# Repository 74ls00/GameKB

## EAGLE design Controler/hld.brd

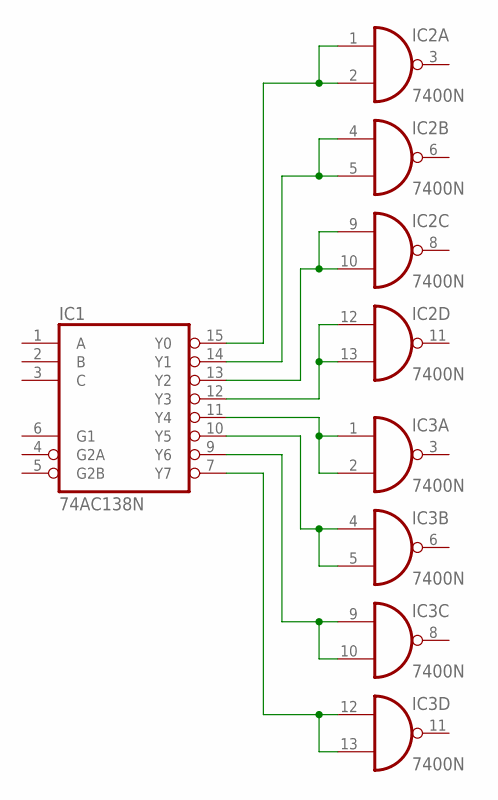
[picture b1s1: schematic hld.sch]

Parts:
IC1: 74AC138N; DIL16
IC2, IC3: 7400N; DIL14

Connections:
GND: IC1.8 (GND), IC2.7 (GND), IC3.7 (GND)
unnamed: IC1.15 (Y0), IC2.1 (I0), IC2.2 (I1)
unnamed: IC1.14 (Y1), IC2.4 (I0), IC2.5 (I1)
unnamed: IC1.13 (Y2), IC2.9 (I0), IC2.10 (I1)
unnamed: IC1.12 (Y3), IC2.12 (I0), IC2.13 (I1)
unnamed: IC1.11 (Y4), IC3.1 (I0), IC3.2 (I1)
unnamed: IC1.10 (Y5), IC3.4 (I0), IC3.5 (I1)
unnamed: IC1.9 (Y6), IC3.9 (I0), IC3.10 (I1)
unnamed: IC1.7 (Y7), IC3.12 (I0), IC3.13 (I1)
VCC: IC1.16 (VCC), IC2.14 (VCC), IC3.14 (VCC)

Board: 2 copper layers, 3 parts (0 on the bottom side), 10 nets, no tracks yet.

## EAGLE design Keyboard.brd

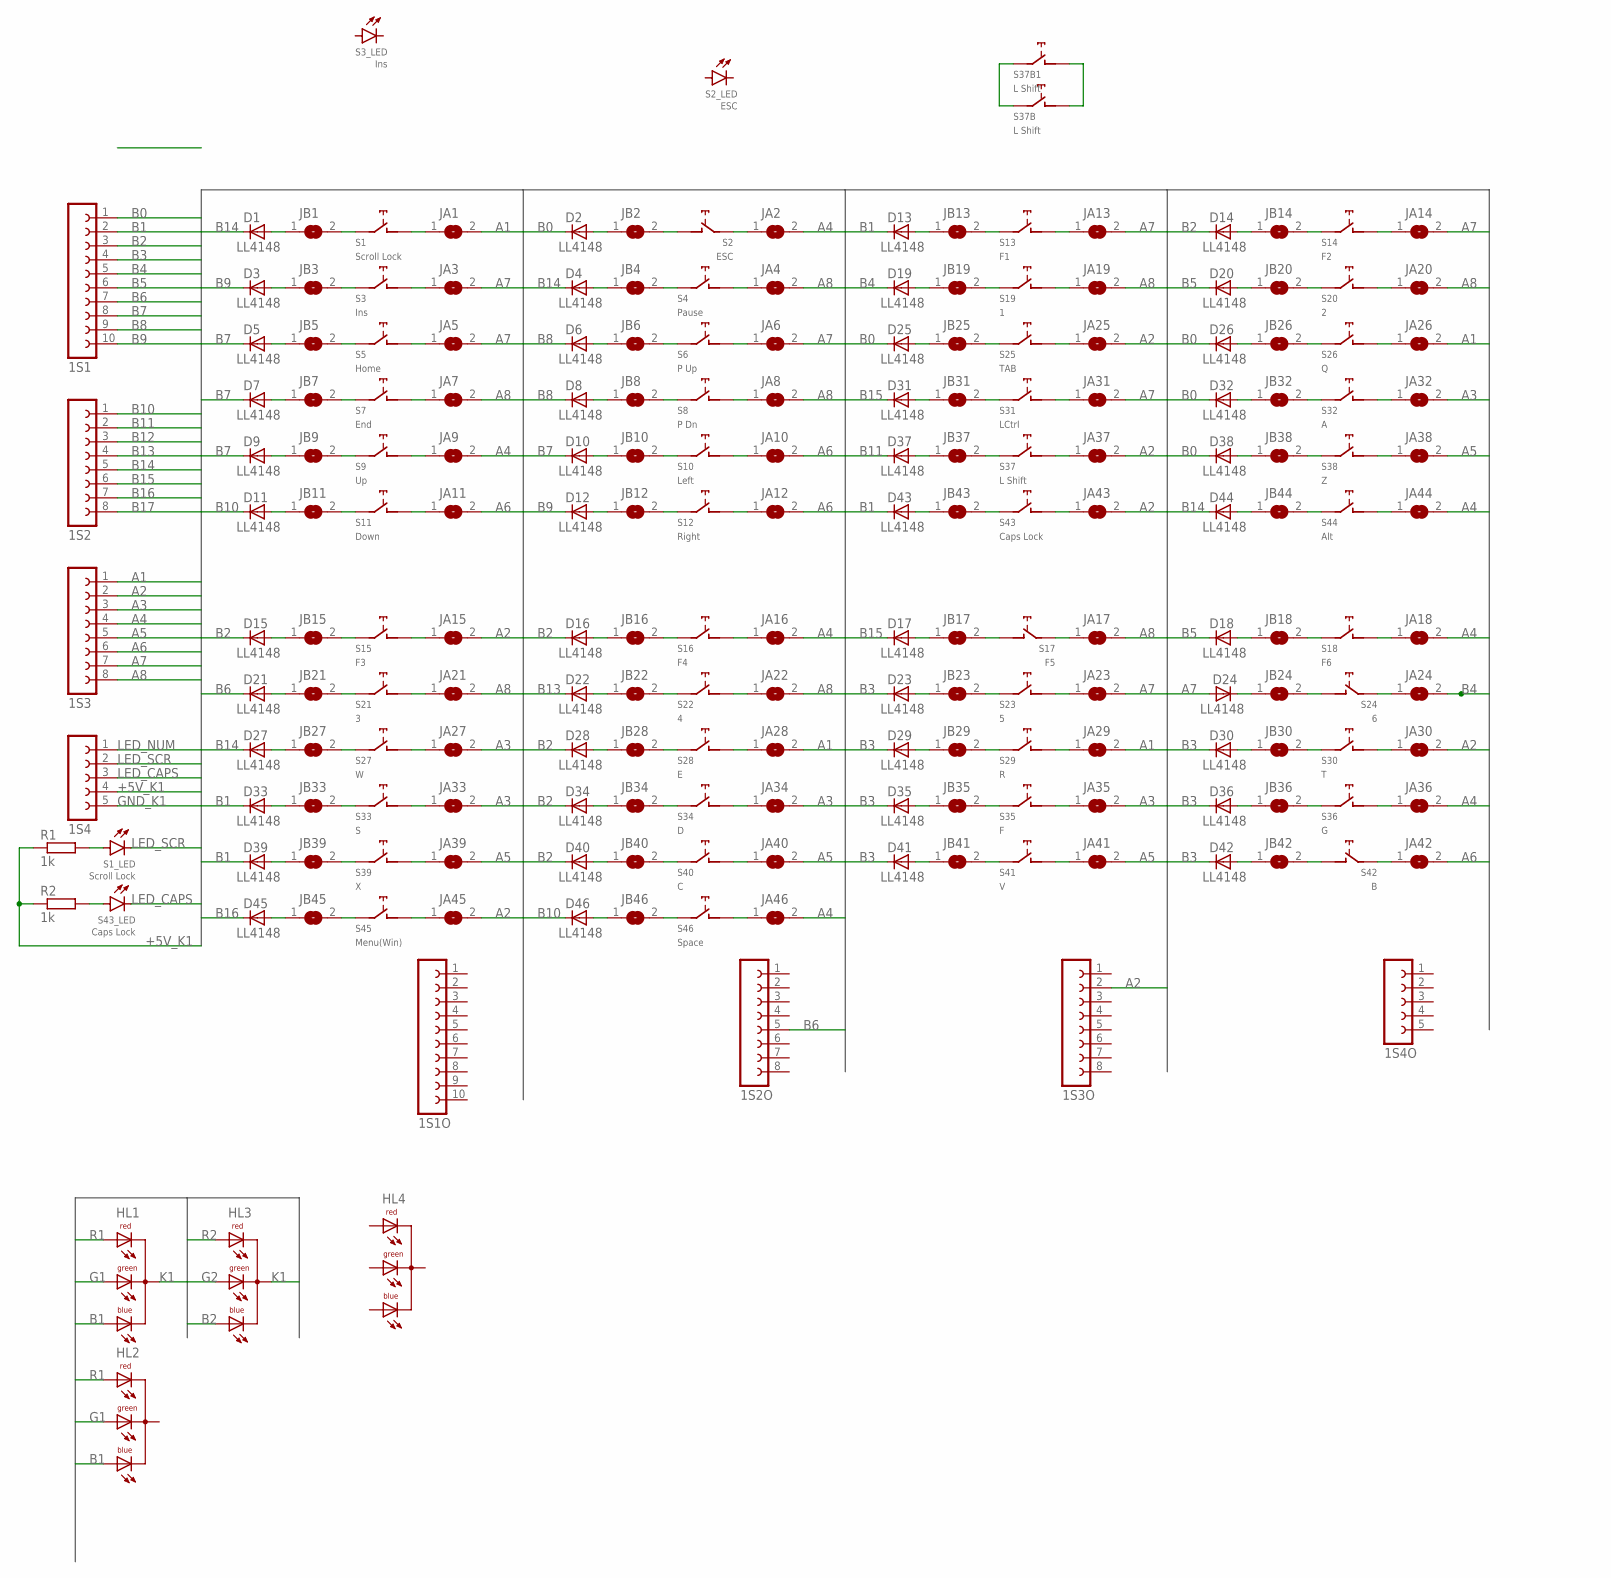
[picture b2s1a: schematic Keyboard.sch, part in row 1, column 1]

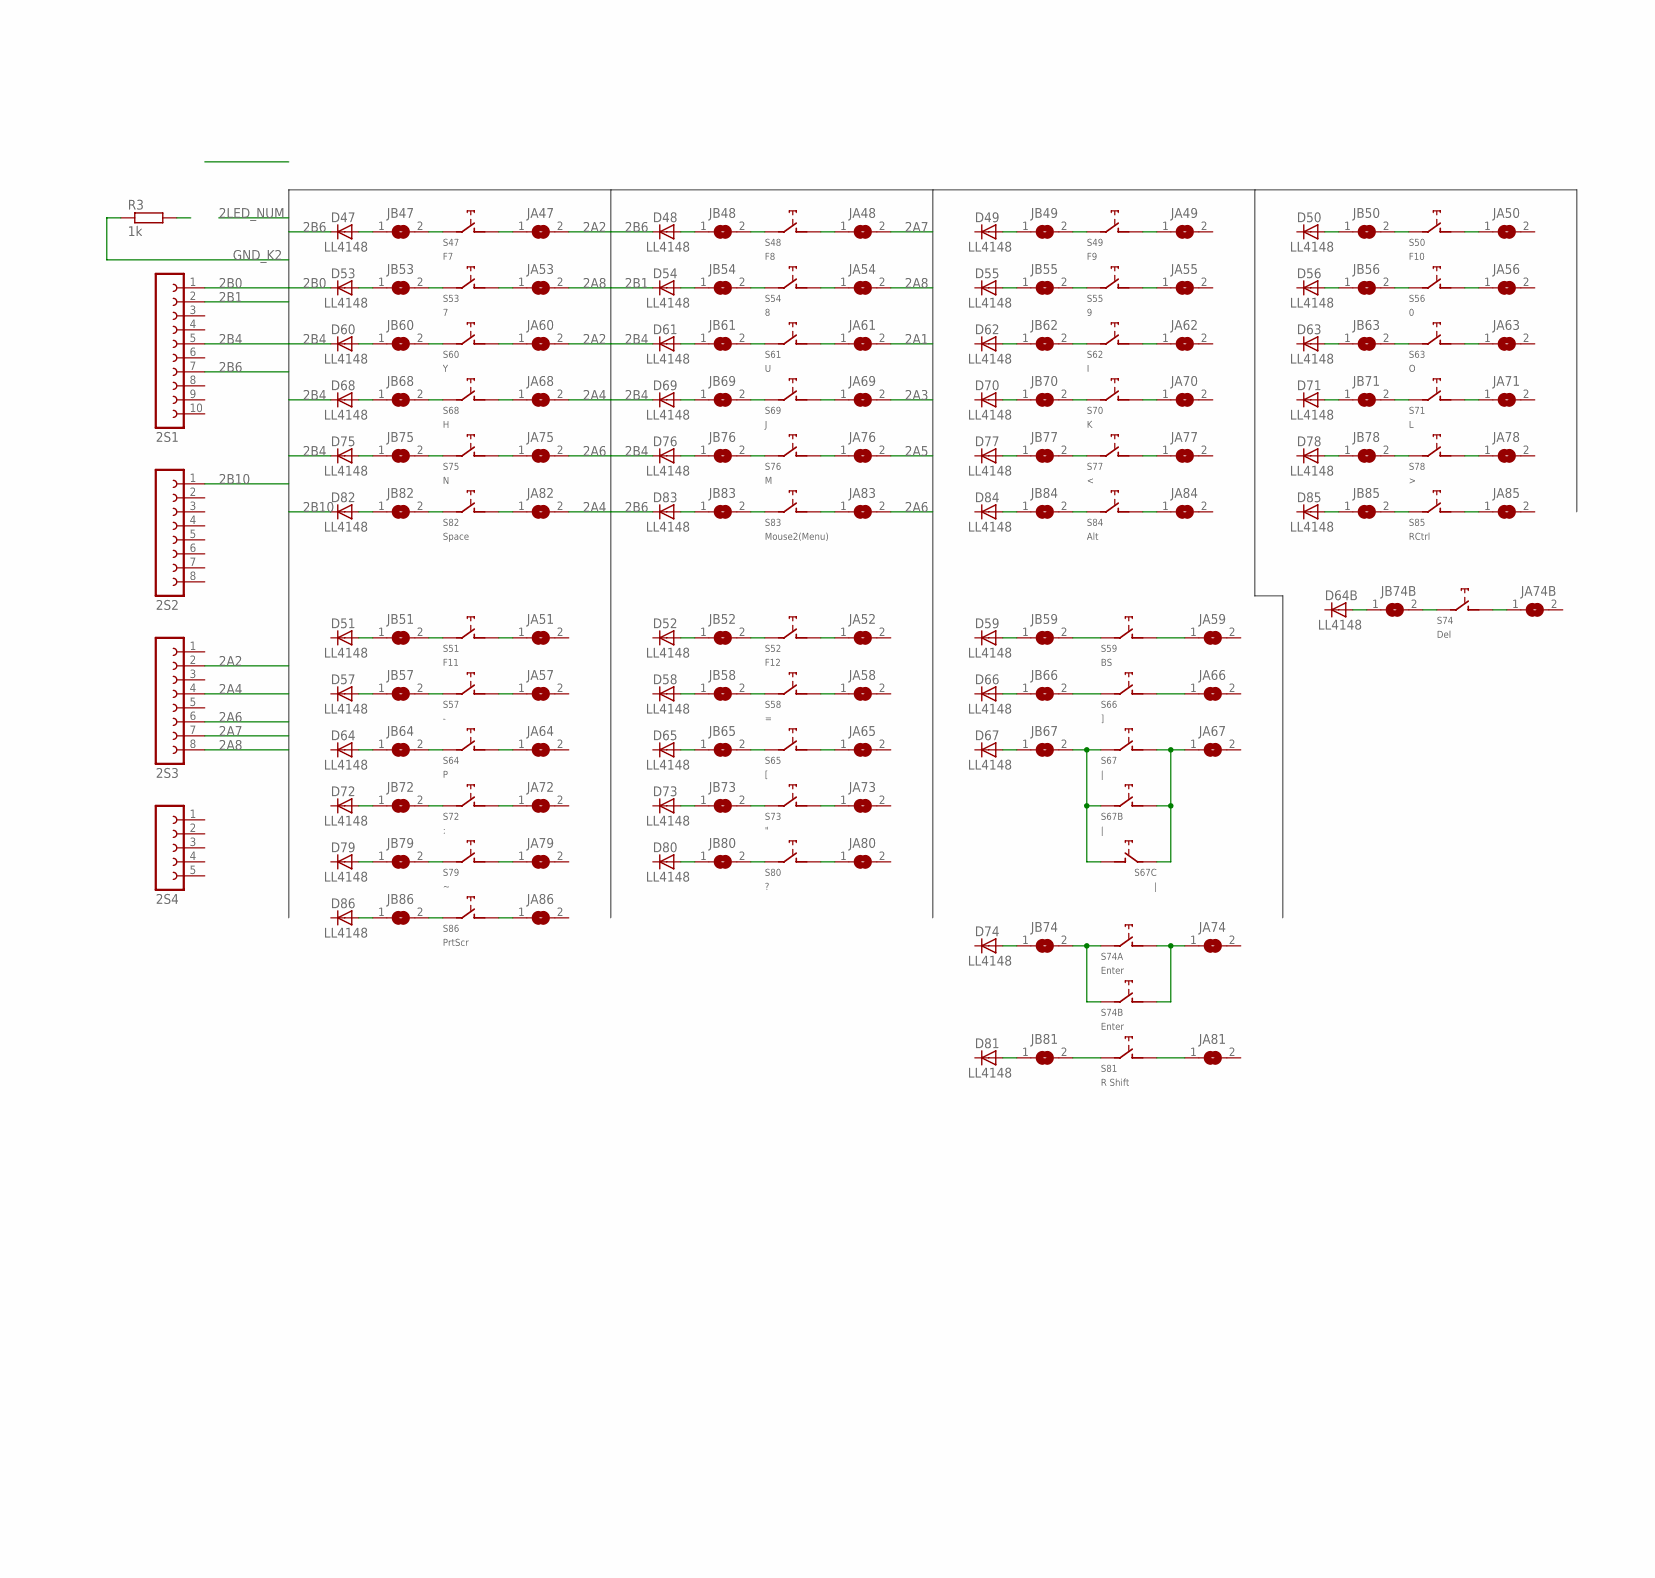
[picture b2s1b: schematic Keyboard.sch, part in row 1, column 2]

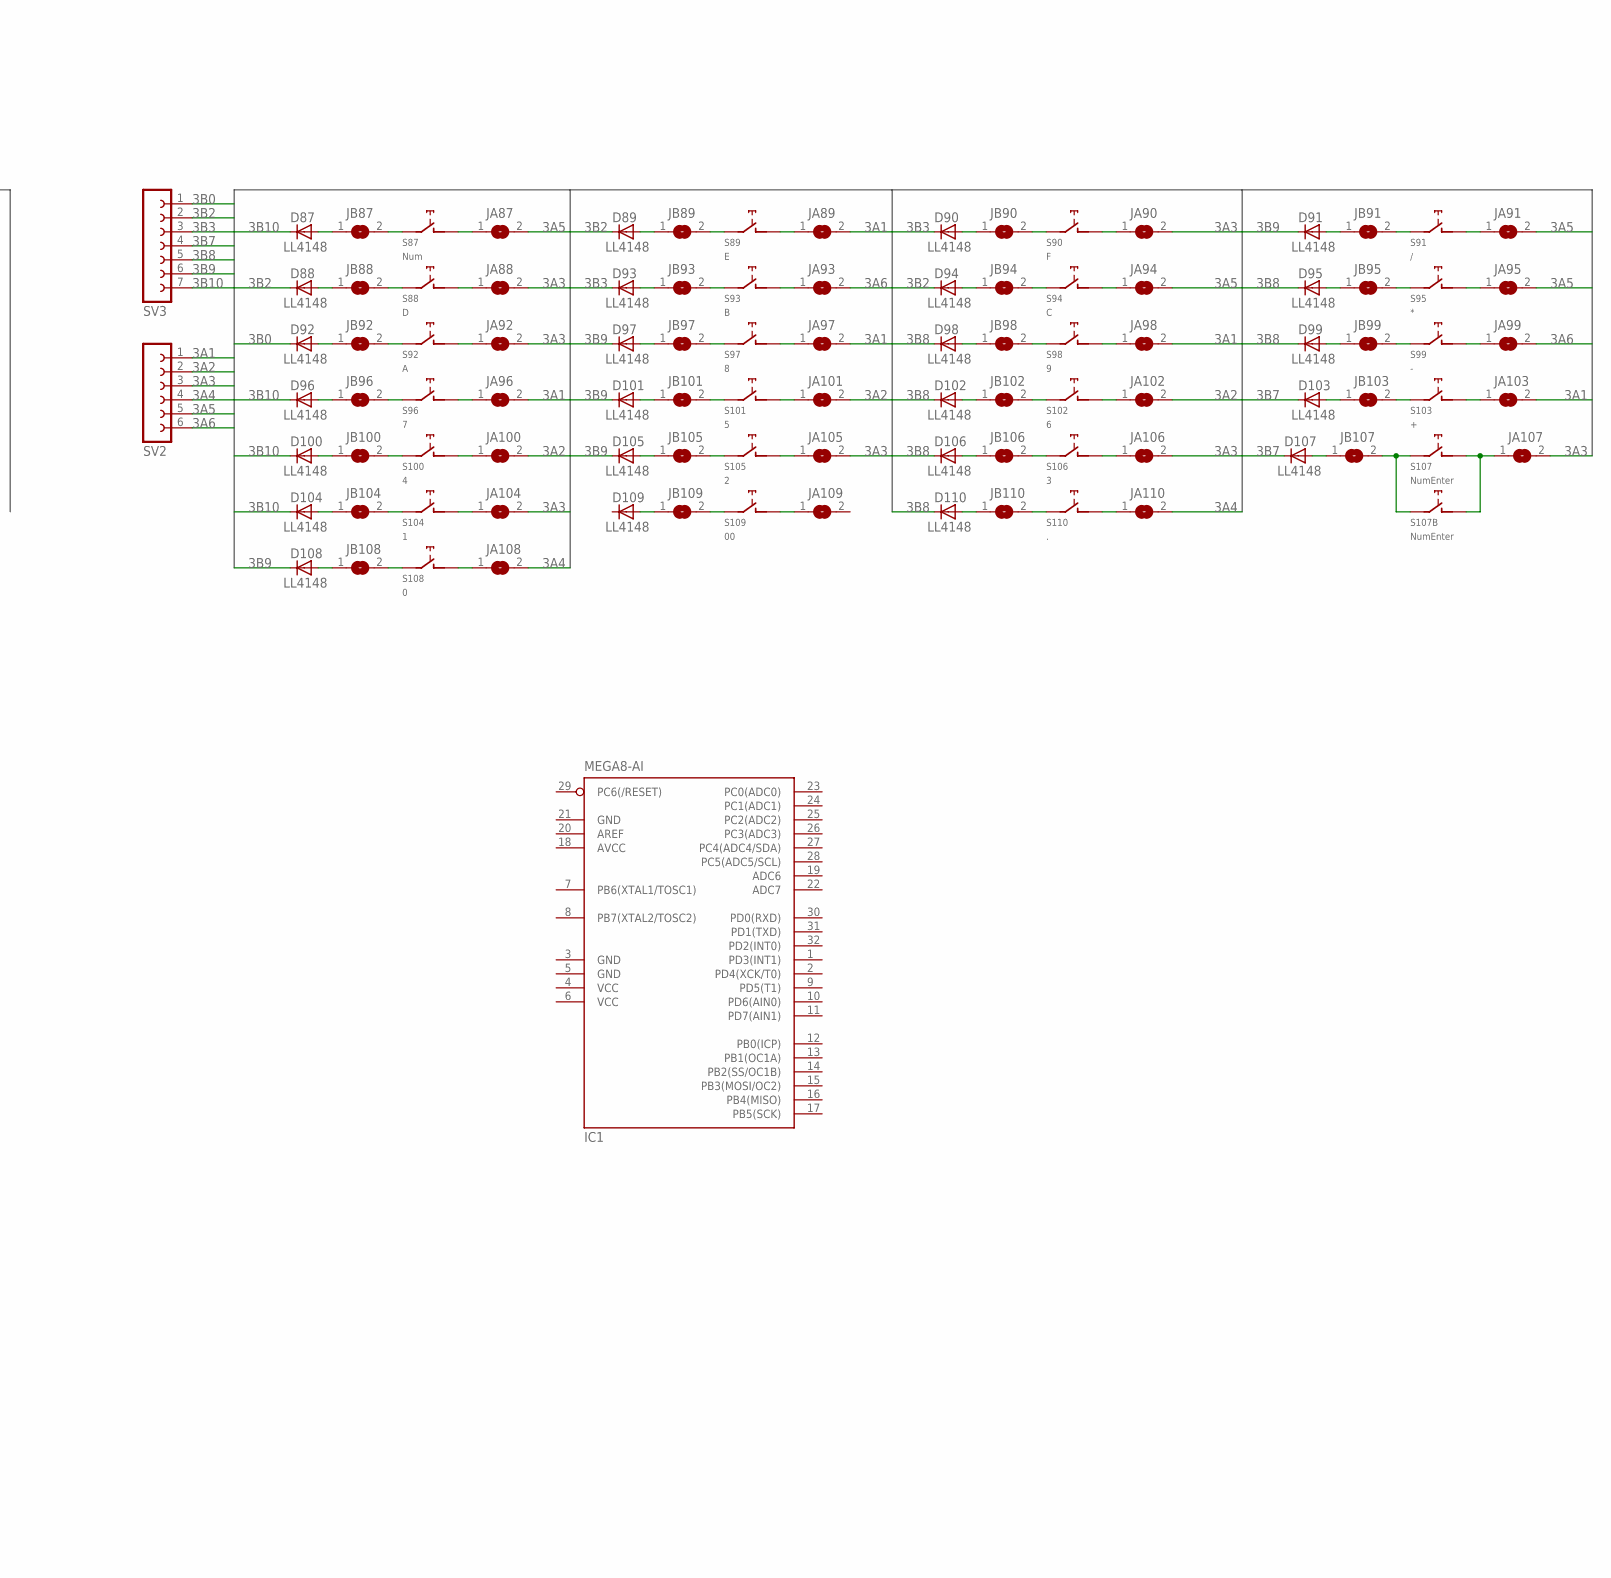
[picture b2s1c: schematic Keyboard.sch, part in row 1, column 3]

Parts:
1S1, 1S1O, 2S1: FE10-1; FE10
1S2, 1S2O, 1S3, 1S3O, 2S2, 2S3: FE08-1; FE08
1S4, 1S4O, 2S4: FE05-1
D1, D2, D3, D4, D5, D6, D7, D8, D9, D10, D11, D12, D13, D14, D15, D16, D17, D18, D19, D20, D21, D22, D23, D24, D25, D26, D27, D28, D29, D30, D31, D32, D33, D34, D35, D36, D37, D38, D39, D40, D41, D42, D43, D44, D45, D46, D47, D48, D49, D50, D51, D52, D53, D54, D55, D56, D57, D58, D59, D60, D61, D62, D63, D64, D64B, D65, D66, D67, D68, D69, D70, D71, D72, D73, D74, D75, D76, D77, D78, D79, D80, D81, D82, D83, D84, D85, D86, D87, D88, D89, D90, D91, D92, D93, D94, D95, D96, D97, D98, D99, D100, D101, D102, D103, D104, D105, D106, D107, D108, D109, D110: LL4148; SOD80C
HL1, HL2, HL3, HL4: RGB2X5
IC1: MEGA8-AI; TQFP32-08
JA1, JA2, JA3, JA4, JA5, JA6, JA7, JA8, JA9, JA10, JA11, JA12: SJ; SJ@1
JA13, JA14, JA15, JA16, JA17, JA18, JA19, JA20, JA21, JA22, JA23, JA24, JA25, JA26, JA27, JA28, JA29, JA30, JA31, JA32, JA33, JA34, JA35, JA36, JA37, JA38, JA39, JA40, JA41, JA42, JA43, JA44, JA45, JA46, JA47, JA48, JA49, JA50, JA51, JA52, JA53, JA54, JA55, JA56, JA57, JA58, JA59, JA60, JA61, JA62, JA63, JA64, JA65, JA66, JA67, JA68, JA69, JA70, JA71, JA72, JA73, JA74, JA74B, JA75, JA76, JA77, JA78, JA79, JA80, JA81, JA82, JA83, JA84, JA85, JA86, JA87, JA88, JA89, JA90, JA91, JA92, JA93, JA94, JA95, JA96, JA97, JA98, JA99, JA100, JA101, JA102, JA103, JA104, JA105, JA106, JA107, JA108, JA109, JA110: SJ
JB1, JB3, JB18, JB19, JB20, JB21, JB22, JB23, JB24, JB25, JB26, JB27, JB28, JB29, JB30, JB31, JB32, JB33, JB34, JB35, JB36, JB37, JB38, JB39, JB40, JB41, JB42, JB43, JB44, JB45, JB46, JB47, JB48, JB49, JB50, JB51, JB52, JB53, JB54, JB55, JB56, JB57, JB58, JB59, JB60, JB61, JB62, JB63, JB64, JB65, JB66, JB67, JB68, JB69, JB70, JB71, JB72, JB73, JB74, JB74B, JB75, JB76, JB77, JB78, JB79, JB80, JB81, JB82, JB83, JB84, JB85, JB86, JB87, JB88, JB89, JB90, JB91, JB92, JB93, JB94, JB95, JB96, JB97, JB98, JB99, JB100, JB101, JB102, JB103, JB104, JB105, JB106, JB107, JB108, JB109, JB110: SJ
JB2, JB4, JB5, JB6, JB7, JB8, JB9, JB10, JB11, JB12, JB13, JB14, JB15, JB16, JB17: SJ; SJ@1
R1, R2: 1k; R1206W
R3: 1k; R0805
S1: Scroll Lock; CHERRY-MX-LED
S2: ESC; CHERRY-MX-LED
S3: Ins; CHERRY-MX-LED
S4: Pause; CHERRY-MX@1
S5: Home; CHERRY-MX
S6: P Up; CHERRY-MX
S7: End; CHERRY-MX
S8: P Dn; CHERRY-MX
S9: Up; CHERRY-MX
S10: Left; CHERRY-MX
S11: Down; CHERRY-MX
S12: Right; CHERRY-MX
S13: F1; CHERRY-MX
S14: F2; CHERRY-MX
S15: F3; CHERRY-MX
S16: F4; CHERRY-MX
S17: F5; CHERRY-MX
S18: F6; CHERRY-MX
S19: 1; CHERRY-MX
S20: 2; CHERRY-MX
S21: 3; CHERRY-MX
S22: 4; CHERRY-MX
S23: 5; CHERRY-MX
S24: 6; CHERRY-MX
S25: TAB; CHERRY-MX
S26: Q; CHERRY-MX
S27: W; CHERRY-MX@1
S28: E; CHERRY-MX
S29: R; CHERRY-MX
S30: T; CHERRY-MX
S31: LCtrl; CHERRY-MX
S32: A; CHERRY-MX
S33: S; CHERRY-MX
S34: D; CHERRY-MX
S35: F; CHERRY-MX
S36: G; CHERRY-MX
S37, S37B, S37B1: L Shift; CHERRY-MX
S38: Z; CHERRY-MX
S39: X; CHERRY-MX
S40: C; CHERRY-MX
S41: V; CHERRY-MX
S42: B; CHERRY-MX
S43: Caps Lock; CHERRY-MX-LED
S44, S84: Alt; CHERRY-MX
S45: Menu(Win); CHERRY-MX
S46, S82: Space; CHERRY-MX
S47: F7; CHERRY-MX
S48: F8; CHERRY-MX
S49: F9; CHERRY-MX
S50: F10; CHERRY-MX
S51: F11; CHERRY-MX
S52: F12; CHERRY-MX
S53: 7; CHERRY-MX
S54: 8; CHERRY-MX
S55: 9; CHERRY-MX
S56: 0; CHERRY-MX
S57: -; CHERRY-MX
S58: =; CHERRY-MX
S59: BS; CHERRY-MX
S60: Y; CHERRY-MX
S61: U; CHERRY-MX
S62: I; CHERRY-MX
S63: O; CHERRY-MX
S64: P; CHERRY-MX
S65: [; CHERRY-MX
S66: ]; CHERRY-MX
S67, S67B, S67C: |; CHERRY-MX
S68: H; CHERRY-MX
S69: J; CHERRY-MX
S70: K; CHERRY-MX
S71: L; CHERRY-MX
S72: :; CHERRY-MX
S73: "; CHERRY-MX
S74: Del; CHERRY-MX
S74A, S74B: Enter; CHERRY-MX
S75: N; CHERRY-MX
S76: M; CHERRY-MX
S77: <; CHERRY-MX
S78: >; CHERRY-MX
S79: CHERRY-MX
S80: ?; CHERRY-MX
S81: R Shift; CHERRY-MX
S83: Mouse2(Menu); CHERRY-MX
S85: RCtrl; CHERRY-MX
S86: PrtScr; CHERRY-MX
S87: Num; CHERRY-MX-4P
S88: D; CHERRY-MX-4P
S89: E; CHERRY-MX-4P
S90: F; CHERRY-MX-4P
S91: /; CHERRY-MX-4P
S92: A; CHERRY-MX-4P
S93: B; CHERRY-MX-4P
S94: C; CHERRY-MX-4P
S95: *; CHERRY-MX-4P
S96: 7; CHERRY-MX-4P
S97: 8; CHERRY-MX-4P
S98: 9; CHERRY-MX-4P
S99: -; CHERRY-MX-4P
S100: 4; CHERRY-MX-4P
S101: 5; CHERRY-MX-4P
S102: 6; CHERRY-MX-4P
S103: +; CHERRY-MX-4P
S104: 1; CHERRY-MX-4P
S105: 2; CHERRY-MX-4P
S106: 3; CHERRY-MX-4P
S107: NumEnter; CHERRY-MX-4P
S107B: NumEnter; CHERRY-MX
S108: 0; CHERRY-MX-4P
S109: 00; CHERRY-MX-4P
S110: .; CHERRY-MX-4P
SV2: FE06-1; FE06
SV3: FE07-1; FE07

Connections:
2A1: JA61.2
2A2: 2S3.2, JA47.2, JA60.2
2A3: JA69.2
2A4: 2S3.4, JA68.2, JA82.2
2A5: JA76.2
2A6: 2S3.6, JA75.2, JA83.2
2A7: 2S3.7, JA48.2
2A8: 2S3.8, JA53.2, JA54.2
2B0: 2S1.1, D53.C
2B1: 2S1.2, D54.C
2B4: 2S1.5, D60.C, D61.C, D68.C, D69.C, D75.C, D76.C
2B6: 2S1.7, D47.C, D48.C, D83.C
2B10: 2S2.1, D82.C
3A1: JA89.2, JA96.2, JA97.2, JA98.2, JA103.2, SV2.1
3A2: JA100.2, JA101.2, JA102.2, SV2.2
3A3: JA88.2, JA90.2, JA92.2, JA104.2, JA105.2, JA106.2, JA107.2, SV2.3
3A4: JA108.2, JA110.2, SV2.4
3A5: JA87.2, JA91.2, JA94.2, JA95.2, SV2.5
3A6: JA93.2, JA99.2, SV2.6
3B0: D92.C, SV3.1
3B2: D88.C, D89.C, D94.C, SV3.2
3B3: D90.C, D93.C, SV3.3
3B7: D103.C, D107.C, SV3.4
3B8: D95.C, D98.C, D99.C, D102.C, D106.C, D110.C, SV3.5
3B9: D91.C, D97.C, D101.C, D105.C, D108.C, SV3.6
3B10: D87.C, D96.C, D100.C, D104.C, SV3.7
+5V_K1: 1S4.4, R1.1, R2.1
A1: 1S3.1, JA1.2, JA26.2, JA28.2, JA29.2
A2: 1S3.2, 1S3O.2, JA15.2, JA25.2, JA30.2, JA37.2, JA43.2, JA45.2
A3: 1S3.3, JA27.2, JA32.2, JA33.2, JA34.2, JA35.2
A4: 1S3.4, JA2.2, JA9.2, JA16.2, JA18.2, JA36.2, JA44.2, JA46.2
A5: 1S3.5, JA38.2, JA39.2, JA40.2, JA41.2
A6: 1S3.6, JA10.2, JA11.2, JA12.2, JA42.2
A7: 1S3.7, D24.A, JA3.2, JA5.2, JA6.2, JA13.2, JA14.2, JA23.2, JA31.2
A8: 1S3.8, JA4.2, JA7.2, JA8.2, JA17.2, JA19.2, JA20.2, JA21.2, JA22.2
AVCC: IC1.18 (AVCC)
B0: 1S1.1, D2.C, D25.C, D26.C, D32.C, D38.C
B1: 1S1.2, D13.C, D33.C, D39.C, D43.C, HL1.4 (AB), HL2.4 (AB)
B2: 1S1.3, D14.C, D15.C, D16.C, D28.C, D34.C, D40.C, HL3.4 (AB)
B3: 1S1.4, D23.C, D29.C, D30.C, D35.C, D36.C, D41.C, D42.C
B4: 1S1.5, D19.C, JA24.2
B5: 1S1.6, D18.C, D20.C
B6: 1S1.7, 1S2O.5, D21.C
B7: 1S1.8, D5.C, D7.C, D9.C, D10.C
B8: 1S1.9, D6.C, D8.C
B9: 1S1.10, D3.C, D12.C
B10: 1S2.1, D11.C, D46.C
B11: 1S2.2, D37.C
B12: 1S2.3
B13: 1S2.4, D22.C
B14: 1S2.5, D1.C, D4.C, D27.C, D44.C
B15: 1S2.6, D17.C, D31.C
B16: 1S2.7, D45.C
B17: 1S2.8
G1: HL1.3 (AG), HL2.3 (AG)
G2: HL3.3 (AG)
GND: IC1.3 (GND), IC1.5 (GND), IC1.21 (GND)
GND_K1: 1S4.5
GND_K2: R3.1
K1: HL1.2 (C), HL3.2 (C)
LED_CAPS: 1S4.3, S43.LED2
LED_NUM: 1S4.1
LED_SCR: 1S4.2, S1.LED2
unnamed: D15.A, JB15.1
unnamed: JB4.2, S4.SW1 (PIN-1)
unnamed: D1.A, JB1.1
unnamed: JA4.1, S4.SW2 (PIN-2)
unnamed: JB14.2, S14.SW1 (PIN-1)
unnamed: JB20.2, S20.SW1 (PIN-1)
unnamed: JB32.2, S32.SW1 (PIN-1)
unnamed: JB38.2, S38.SW1 (PIN-1)
unnamed: JB6.2, S6.SW1 (PIN-1)
unnamed: JA6.1, S6.SW2 (PIN-2)
unnamed: JA8.1, S8.SW2 (PIN-2)
unnamed: JB8.2, S8.SW1 (PIN-1)
unnamed: JB10.2, S10.SW1 (PIN-1)
unnamed: JB1.2, S1.SW1 (PIN-1)
unnamed: D2.A, JB2.1
unnamed: JB2.2, S2.SW2 (PIN-2)
unnamed: JA2.1, S2.SW1 (PIN-1)
unnamed: D16.A, JB16.1
unnamed: JB3.2, S3.SW1 (PIN-1)
unnamed: JB5.2, S5.SW1 (PIN-1)
unnamed: JB7.2, S7.SW1 (PIN-1)
unnamed: JB9.2, S9.SW1 (PIN-1)
unnamed: JB11.2, S11.SW1 (PIN-1)
unnamed: D3.A, JB3.1
unnamed: JB12.2, S12.SW1 (PIN-1)
unnamed: D5.A, JB5.1
unnamed: D7.A, JB7.1
unnamed: JA10.1, S10.SW2 (PIN-2)
unnamed: JA1.1, S1.SW2 (PIN-2)
unnamed: D9.A, JB9.1
unnamed: D11.A, JB11.1
unnamed: JA3.1, S3.SW2 (PIN-2)
unnamed: JA5.1, S5.SW2 (PIN-2)
unnamed: JA7.1, S7.SW2 (PIN-2)
unnamed: JA9.1, S9.SW2 (PIN-2)
unnamed: JA11.1, S11.SW2 (PIN-2)
unnamed: JA12.1, S12.SW2 (PIN-2)
unnamed: JA14.1, S14.SW2 (PIN-2)
unnamed: JB13.2, S13.SW1 (PIN-1)
unnamed: JA13.1, S13.SW2 (PIN-2)
unnamed: D14.A, JB14.1
unnamed: JB42.2, S42.SW2 (PIN-2)
unnamed: JA42.1, S42.SW1 (PIN-1)
unnamed: JB27.2, S27.SW1 (PIN-1)
unnamed: JA27.1, S27.SW2 (PIN-2)
unnamed: JB17.2, S17.SW2 (PIN-2)
unnamed: JA17.1, S17.SW1 (PIN-1)
unnamed: D24.C, JB24.1
unnamed: JB24.2, S24.SW2 (PIN-2)
unnamed: JA24.1, S24.SW1 (PIN-1)
unnamed: JA107.1, S107.SW2 (PIN-2), S107B.SW2 (PIN-2)
unnamed: D4.A, JB4.1
unnamed: D6.A, JB6.1
unnamed: D8.A, JB8.1
unnamed: D10.A, JB10.1
unnamed: D12.A, JB12.1
unnamed: D13.A, JB13.1
unnamed: JB19.2, S19.SW1 (PIN-1)
unnamed: JB25.2, S25.SW1 (PIN-1)
unnamed: D104.A, JB104.1
unnamed: JB31.2, S31.SW1 (PIN-1)
unnamed: JB37.2, S37.SW1 (PIN-1), S37B.SW1 (PIN-1), S37B1.SW1 (PIN-1)
unnamed: JB43.2, S43.SW1 (PIN-1)
unnamed: JB26.2, S26.SW1 (PIN-1)
unnamed: JB44.2, S44.SW1 (PIN-1)
unnamed: JB18.2, S18.SW1 (PIN-1)
unnamed: JB30.2, S30.SW1 (PIN-1)
unnamed: JB36.2, S36.SW1 (PIN-1)
unnamed: JB74B.2, S74.SW1 (PIN-1)
unnamed: JB52.2, S52.SW1 (PIN-1)
unnamed: JB23.2, S23.SW1 (PIN-1)
unnamed: JB29.2, S29.SW1 (PIN-1)
unnamed: JB35.2, S35.SW1 (PIN-1)
unnamed: JB41.2, S41.SW1 (PIN-1)
unnamed: JB16.2, S16.SW1 (PIN-1)
unnamed: JB22.2, S22.SW1 (PIN-1)
unnamed: JB28.2, S28.SW1 (PIN-1)
unnamed: JB34.2, S34.SW1 (PIN-1)
unnamed: JB40.2, S40.SW1 (PIN-1)
unnamed: JB46.2, S46.SW1 (PIN-1)
unnamed: JB15.2, S15.SW1 (PIN-1)
unnamed: JB21.2, S21.SW1 (PIN-1)
unnamed: JB63.2, S63.SW1 (PIN-1)
unnamed: JB33.2, S33.SW1 (PIN-1)
unnamed: JB39.2, S39.SW1 (PIN-1)
unnamed: JB45.2, S45.SW1 (PIN-1)
unnamed: JA15.1, S15.SW2 (PIN-2)
unnamed: JB73.2, S73.SW1 (PIN-1)
unnamed: JA18.1, S18.SW2 (PIN-2)
unnamed: JA20.1, S20.SW2 (PIN-2)
unnamed: JA22.1, S22.SW2 (PIN-2)
unnamed: JA23.1, S23.SW2 (PIN-2)
unnamed: JB74.2, S74A.SW1 (PIN-1), S74B.SW1 (PIN-1)
unnamed: JA25.1, S25.SW2 (PIN-2)
unnamed: JA26.1, S26.SW2 (PIN-2)
unnamed: JA74.1, S74A.SW2 (PIN-2), S74B.SW2 (PIN-2)
unnamed: JA28.1, S28.SW2 (PIN-2)
unnamed: JA29.1, S29.SW2 (PIN-2)
unnamed: JA30.1, S30.SW2 (PIN-2)
unnamed: JA31.1, S31.SW2 (PIN-2)
unnamed: JA32.1, S32.SW2 (PIN-2)
unnamed: JA33.1, S33.SW2 (PIN-2)
unnamed: JA34.1, S34.SW2 (PIN-2)
unnamed: JA35.1, S35.SW2 (PIN-2)
unnamed: JA36.1, S36.SW2 (PIN-2)
unnamed: JA37.1, S37.SW2 (PIN-2), S37B.SW2 (PIN-2), S37B1.SW2 (PIN-2)
unnamed: JA38.1, S38.SW2 (PIN-2)
unnamed: JA39.1, S39.SW2 (PIN-2)
unnamed: JA40.1, S40.SW2 (PIN-2)
unnamed: JA41.1, S41.SW2 (PIN-2)
unnamed: JB47.2, S47.SW1 (PIN-1)
unnamed: JA43.1, S43.SW2 (PIN-2)
unnamed: JA45.1, S45.SW2 (PIN-2)
unnamed: JA46.1, S46.SW2 (PIN-2)
unnamed: JA19.1, S19.SW2 (PIN-2)
unnamed: JA44.1, S44.SW2 (PIN-2)
unnamed: JA21.1, S21.SW2 (PIN-2)
unnamed: JA16.1, S16.SW2 (PIN-2)
unnamed: D17.A, JB17.1
unnamed: D18.A, JB18.1
unnamed: D19.A, JB19.1
unnamed: D20.A, JB20.1
unnamed: D21.A, JB21.1
unnamed: D22.A, JB22.1
unnamed: D23.A, JB23.1
unnamed: JB53.2, S53.SW1 (PIN-1)
unnamed: D25.A, JB25.1
unnamed: D26.A, JB26.1
unnamed: D27.A, JB27.1
unnamed: D28.A, JB28.1
unnamed: D29.A, JB29.1
unnamed: D30.A, JB30.1
unnamed: D31.A, JB31.1
unnamed: D32.A, JB32.1
unnamed: D33.A, JB33.1
unnamed: D34.A, JB34.1
unnamed: D35.A, JB35.1
unnamed: D36.A, JB36.1
unnamed: D37.A, JB37.1
unnamed: D38.A, JB38.1
unnamed: D39.A, JB39.1
unnamed: D40.A, JB40.1
unnamed: D41.A, JB41.1
unnamed: D42.A, JB42.1
unnamed: D43.A, JB43.1
unnamed: D44.A, JB44.1
unnamed: D45.A, JB45.1
unnamed: D46.A, JB46.1
unnamed: R1.2, S1.LED1
unnamed: R2.2, S43.LED1
unnamed: JB60.2, S60.SW1 (PIN-1)
unnamed: JB68.2, S68.SW1 (PIN-1)
unnamed: JB75.2, S75.SW1 (PIN-1)
unnamed: JB82.2, S82.SW1 (PIN-1)
unnamed: JB48.2, S48.SW1 (PIN-1)
unnamed: JB54.2, S54.SW1 (PIN-1)
unnamed: JB61.2, S61.SW1 (PIN-1)
unnamed: JB69.2, S69.SW1 (PIN-1)
unnamed: JB76.2, S76.SW1 (PIN-1)
unnamed: JB83.2, S83.SW1 (PIN-1)
unnamed: JB49.2, S49.SW1 (PIN-1)
unnamed: JB55.2, S55.SW1 (PIN-1)
unnamed: JB62.2, S62.SW1 (PIN-1)
unnamed: JB70.2, S70.SW1 (PIN-1)
unnamed: JB77.2, S77.SW1 (PIN-1)
unnamed: JB84.2, S84.SW1 (PIN-1)
unnamed: JB50.2, S50.SW1 (PIN-1)
unnamed: JB56.2, S56.SW1 (PIN-1)
unnamed: JB71.2, S71.SW1 (PIN-1)
unnamed: JB78.2, S78.SW1 (PIN-1)
unnamed: JB85.2, S85.SW1 (PIN-1)
unnamed: JB51.2, S51.SW1 (PIN-1)
unnamed: JB57.2, S57.SW1 (PIN-1)
unnamed: JB64.2, S64.SW1 (PIN-1)
unnamed: JB72.2, S72.SW1 (PIN-1)
unnamed: JB79.2, S79.SW1 (PIN-1)
unnamed: JB86.2, S86.SW1 (PIN-1)
unnamed: JB58.2, S58.SW1 (PIN-1)
unnamed: JB65.2, S65.SW1 (PIN-1)
unnamed: JB80.2, S80.SW1 (PIN-1)
unnamed: JB59.2, S59.SW1 (PIN-1)
unnamed: JB66.2, S66.SW1 (PIN-1)
unnamed: JB67.2, S67.SW1 (PIN-1), S67B.SW1 (PIN-1), S67C.SW2 (PIN-2)
unnamed: JB81.2, S81.SW1 (PIN-1)
unnamed: D47.A, JB47.1
unnamed: D53.A, JB53.1
unnamed: D60.A, JB60.1
unnamed: D68.A, JB68.1
unnamed: D75.A, JB75.1
unnamed: D82.A, JB82.1
unnamed: D48.A, JB48.1
unnamed: D54.A, JB54.1
unnamed: D61.A, JB61.1
unnamed: D69.A, JB69.1
unnamed: D76.A, JB76.1
unnamed: D83.A, JB83.1
unnamed: D49.A, JB49.1
unnamed: D55.A, JB55.1
unnamed: D62.A, JB62.1
unnamed: D70.A, JB70.1
unnamed: D77.A, JB77.1
unnamed: D84.A, JB84.1
unnamed: D50.A, JB50.1
unnamed: D56.A, JB56.1
unnamed: D63.A, JB63.1
unnamed: D71.A, JB71.1
unnamed: D78.A, JB78.1
unnamed: D85.A, JB85.1
unnamed: D51.A, JB51.1
unnamed: D57.A, JB57.1
unnamed: D64.A, JB64.1
unnamed: D72.A, JB72.1
unnamed: D79.A, JB79.1
unnamed: D86.A, JB86.1
unnamed: D52.A, JB52.1
unnamed: D58.A, JB58.1
unnamed: D65.A, JB65.1
unnamed: D73.A, JB73.1
unnamed: D80.A, JB80.1
unnamed: D59.A, JB59.1
unnamed: D66.A, JB66.1
unnamed: D67.A, JB67.1
unnamed: D74.A, JB74.1
unnamed: D81.A, JB81.1
unnamed: JA66.1, S66.SW2 (PIN-2)
unnamed: JA47.1, S47.SW2 (PIN-2)
unnamed: JA53.1, S53.SW2 (PIN-2)
unnamed: JA60.1, S60.SW2 (PIN-2)
unnamed: JA68.1, S68.SW2 (PIN-2)
unnamed: JA75.1, S75.SW2 (PIN-2)
unnamed: JA82.1, S82.SW2 (PIN-2)
unnamed: JA48.1, S48.SW2 (PIN-2)
unnamed: JA54.1, S54.SW2 (PIN-2)
unnamed: JA61.1, S61.SW2 (PIN-2)
unnamed: JA69.1, S69.SW2 (PIN-2)
unnamed: JA76.1, S76.SW2 (PIN-2)
unnamed: JA83.1, S83.SW2 (PIN-2)
unnamed: JA49.1, S49.SW2 (PIN-2)
unnamed: JA55.1, S55.SW2 (PIN-2)
unnamed: JA62.1, S62.SW2 (PIN-2)
unnamed: JA70.1, S70.SW2 (PIN-2)
unnamed: JA77.1, S77.SW2 (PIN-2)
unnamed: JA84.1, S84.SW2 (PIN-2)
unnamed: JA50.1, S50.SW2 (PIN-2)
unnamed: JA56.1, S56.SW2 (PIN-2)
unnamed: JA63.1, S63.SW2 (PIN-2)
unnamed: JA71.1, S71.SW2 (PIN-2)
unnamed: JA78.1, S78.SW2 (PIN-2)
unnamed: JA85.1, S85.SW2 (PIN-2)
unnamed: JA51.1, S51.SW2 (PIN-2)
unnamed: JA57.1, S57.SW2 (PIN-2)
unnamed: JA64.1, S64.SW2 (PIN-2)
unnamed: JA72.1, S72.SW2 (PIN-2)
unnamed: JA79.1, S79.SW2 (PIN-2)
unnamed: JA86.1, S86.SW2 (PIN-2)
unnamed: JA52.1, S52.SW2 (PIN-2)
unnamed: JA58.1, S58.SW2 (PIN-2)
unnamed: JA65.1, S65.SW2 (PIN-2)
unnamed: JA73.1, S73.SW2 (PIN-2)
unnamed: JA80.1, S80.SW2 (PIN-2)
unnamed: JA81.1, S81.SW2 (PIN-2)
unnamed: JA67.1, S67.SW2 (PIN-2), S67B.SW2 (PIN-2), S67C.SW1 (PIN-1)
unnamed: JA59.1, S59.SW2 (PIN-2)
unnamed: D64B.A, JB74B.1
unnamed: JA74B.1, S74.SW2 (PIN-2)
unnamed: D87.A, JB87.1
unnamed: D88.A, JB88.1
unnamed: JB87.2, S87.SW1 (PIN-1)
unnamed: JB88.2, S88.SW1 (PIN-1)
unnamed: JA87.1, S87.SW2 (PIN-2)
unnamed: JA88.1, S88.SW2 (PIN-2)
unnamed: D89.A, JB89.1
unnamed: JB89.2, S89.SW1 (PIN-1)
unnamed: JA89.1, S89.SW2 (PIN-2)
unnamed: D90.A, JB90.1
unnamed: JB90.2, S90.SW1 (PIN-1)
unnamed: JA90.1, S90.SW2 (PIN-2)
unnamed: D91.A, JB91.1
unnamed: JB91.2, S91.SW1 (PIN-1)
unnamed: JA91.1, S91.SW2 (PIN-2)
unnamed: JB92.2, S92.SW1 (PIN-1)
unnamed: D92.A, JB92.1
unnamed: JA92.1, S92.SW2 (PIN-2)
unnamed: JA93.1, S93.SW2 (PIN-2)
unnamed: JB93.2, S93.SW1 (PIN-1)
unnamed: D93.A, JB93.1
unnamed: D94.A, JB94.1
unnamed: JB94.2, S94.SW1 (PIN-1)
unnamed: JA94.1, S94.SW2 (PIN-2)
unnamed: D95.A, JB95.1
unnamed: JB95.2, S95.SW1 (PIN-1)
unnamed: JA95.1, S95.SW2 (PIN-2)
unnamed: D96.A, JB96.1
unnamed: JB96.2, S96.SW1 (PIN-1)
unnamed: JA96.1, S96.SW2 (PIN-2)
unnamed: JB97.2, S97.SW1 (PIN-1)
unnamed: JA97.1, S97.SW2 (PIN-2)
unnamed: D97.A, JB97.1
unnamed: D98.A, JB98.1
unnamed: JB98.2, S98.SW1 (PIN-1)
unnamed: JA98.1, S98.SW2 (PIN-2)
unnamed: D99.A, JB99.1
unnamed: JB99.2, S99.SW1 (PIN-1)
unnamed: JA99.1, S99.SW2 (PIN-2)
unnamed: D100.A, JB100.1
unnamed: JB100.2, S100.SW1 (PIN-1)
unnamed: JA100.1, S100.SW2 (PIN-2)
unnamed: JB101.2, S101.SW1 (PIN-1)
unnamed: D101.A, JB101.1
unnamed: JA101.1, S101.SW2 (PIN-2)
unnamed: D102.A, JB102.1
unnamed: JB102.2, S102.SW1 (PIN-1)
unnamed: JA102.1, S102.SW2 (PIN-2)
unnamed: D103.A, JB103.1
unnamed: JB103.2, S103.SW1 (PIN-1)
unnamed: JA103.1, S103.SW2 (PIN-2)
unnamed: JB107.2, S107.SW1 (PIN-1), S107B.SW1 (PIN-1)
unnamed: JB104.2, S104.SW1 (PIN-1)
unnamed: JA104.1, S104.SW2 (PIN-2)
unnamed: JB105.2, S105.SW1 (PIN-1)
unnamed: D105.A, JB105.1
unnamed: JA105.1, S105.SW2 (PIN-2)
unnamed: D106.A, JB106.1
unnamed: JB106.2, S106.SW1 (PIN-1)
unnamed: JA106.1, S106.SW2 (PIN-2)
unnamed: D107.A, JB107.1
unnamed: JB108.2, S108.SW1 (PIN-1)
unnamed: JA108.1, S108.SW2 (PIN-2)
unnamed: D108.A, JB108.1
unnamed: JB109.2, S109.SW1 (PIN-1)
unnamed: D109.A, JB109.1
unnamed: JA109.1, S109.SW2 (PIN-2)
unnamed: D110.A, JB110.1
unnamed: JB110.2, S110.SW1 (PIN-1)
unnamed: JA110.1, S110.SW2 (PIN-2)
R1: HL1.1 (AR), HL2.1 (AR)
R2: HL3.1 (AR)
VCC: IC1.4 (VCC), IC1.6 (VCC)

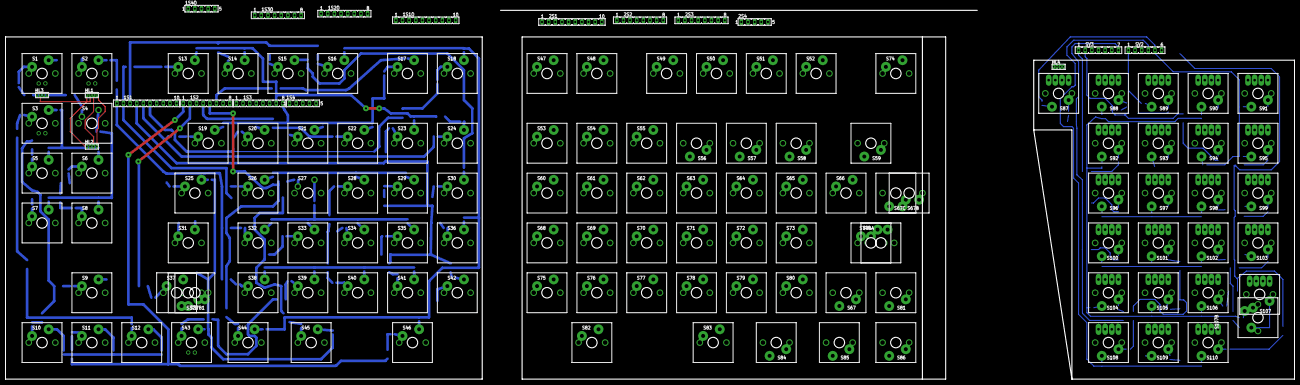
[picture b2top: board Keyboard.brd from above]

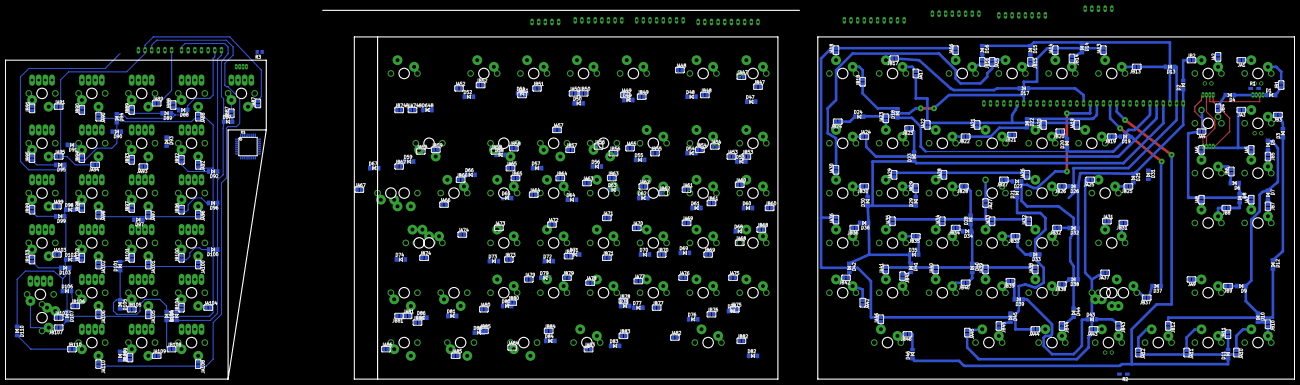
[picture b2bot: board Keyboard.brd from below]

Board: 2 copper layers, 492.8 x 141.0 mm, 588 parts (31 on the bottom side), 390 nets.

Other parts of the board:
U$1, U$2, U$3, U$4, U$5, U$6, U$7, U$8, U$9, U$10, U$11, U$12, U$13, U$14, U$18, U$19, U$20, U$21, U$23, U$24, U$25, U$26, U$27, U$29, U$30, U$31, U$32, U$33, U$35, U$36, U$37, U$38, U$39, U$40, U$41, U$42, U$43, U$44, U$45, U$46, U$47, U$48, U$49, U$50, U$51, U$52, U$53, U$54, U$55, U$56, U$57, U$58, U$59, U$60, U$61, U$62, U$63, U$64, U$65, U$66, U$67, U$68, U$69, U$70, U$71, U$72, U$73, U$74, U$75, U$76, U$77, U$78, U$83, U$87, U$88, U$89, U$90, U$91, U$92, U$93, U$94, U$95, U$96, U$97, U$98, U$99, U$100, U$101, U$102, U$103, U$104, U$105, U$106, U$107, U$108, U$109, U$110, U$116, U$117, U$118: 18X18
U$15, U$16, U$84, U$85, U$86: 18X23
U$17, U$79: 18X52
U$22: 18X42
U$28, U$114: 18X33
U$34, U$113, U$115: 18X28
U$80, U$112: 18X37
U$111: 37X18
